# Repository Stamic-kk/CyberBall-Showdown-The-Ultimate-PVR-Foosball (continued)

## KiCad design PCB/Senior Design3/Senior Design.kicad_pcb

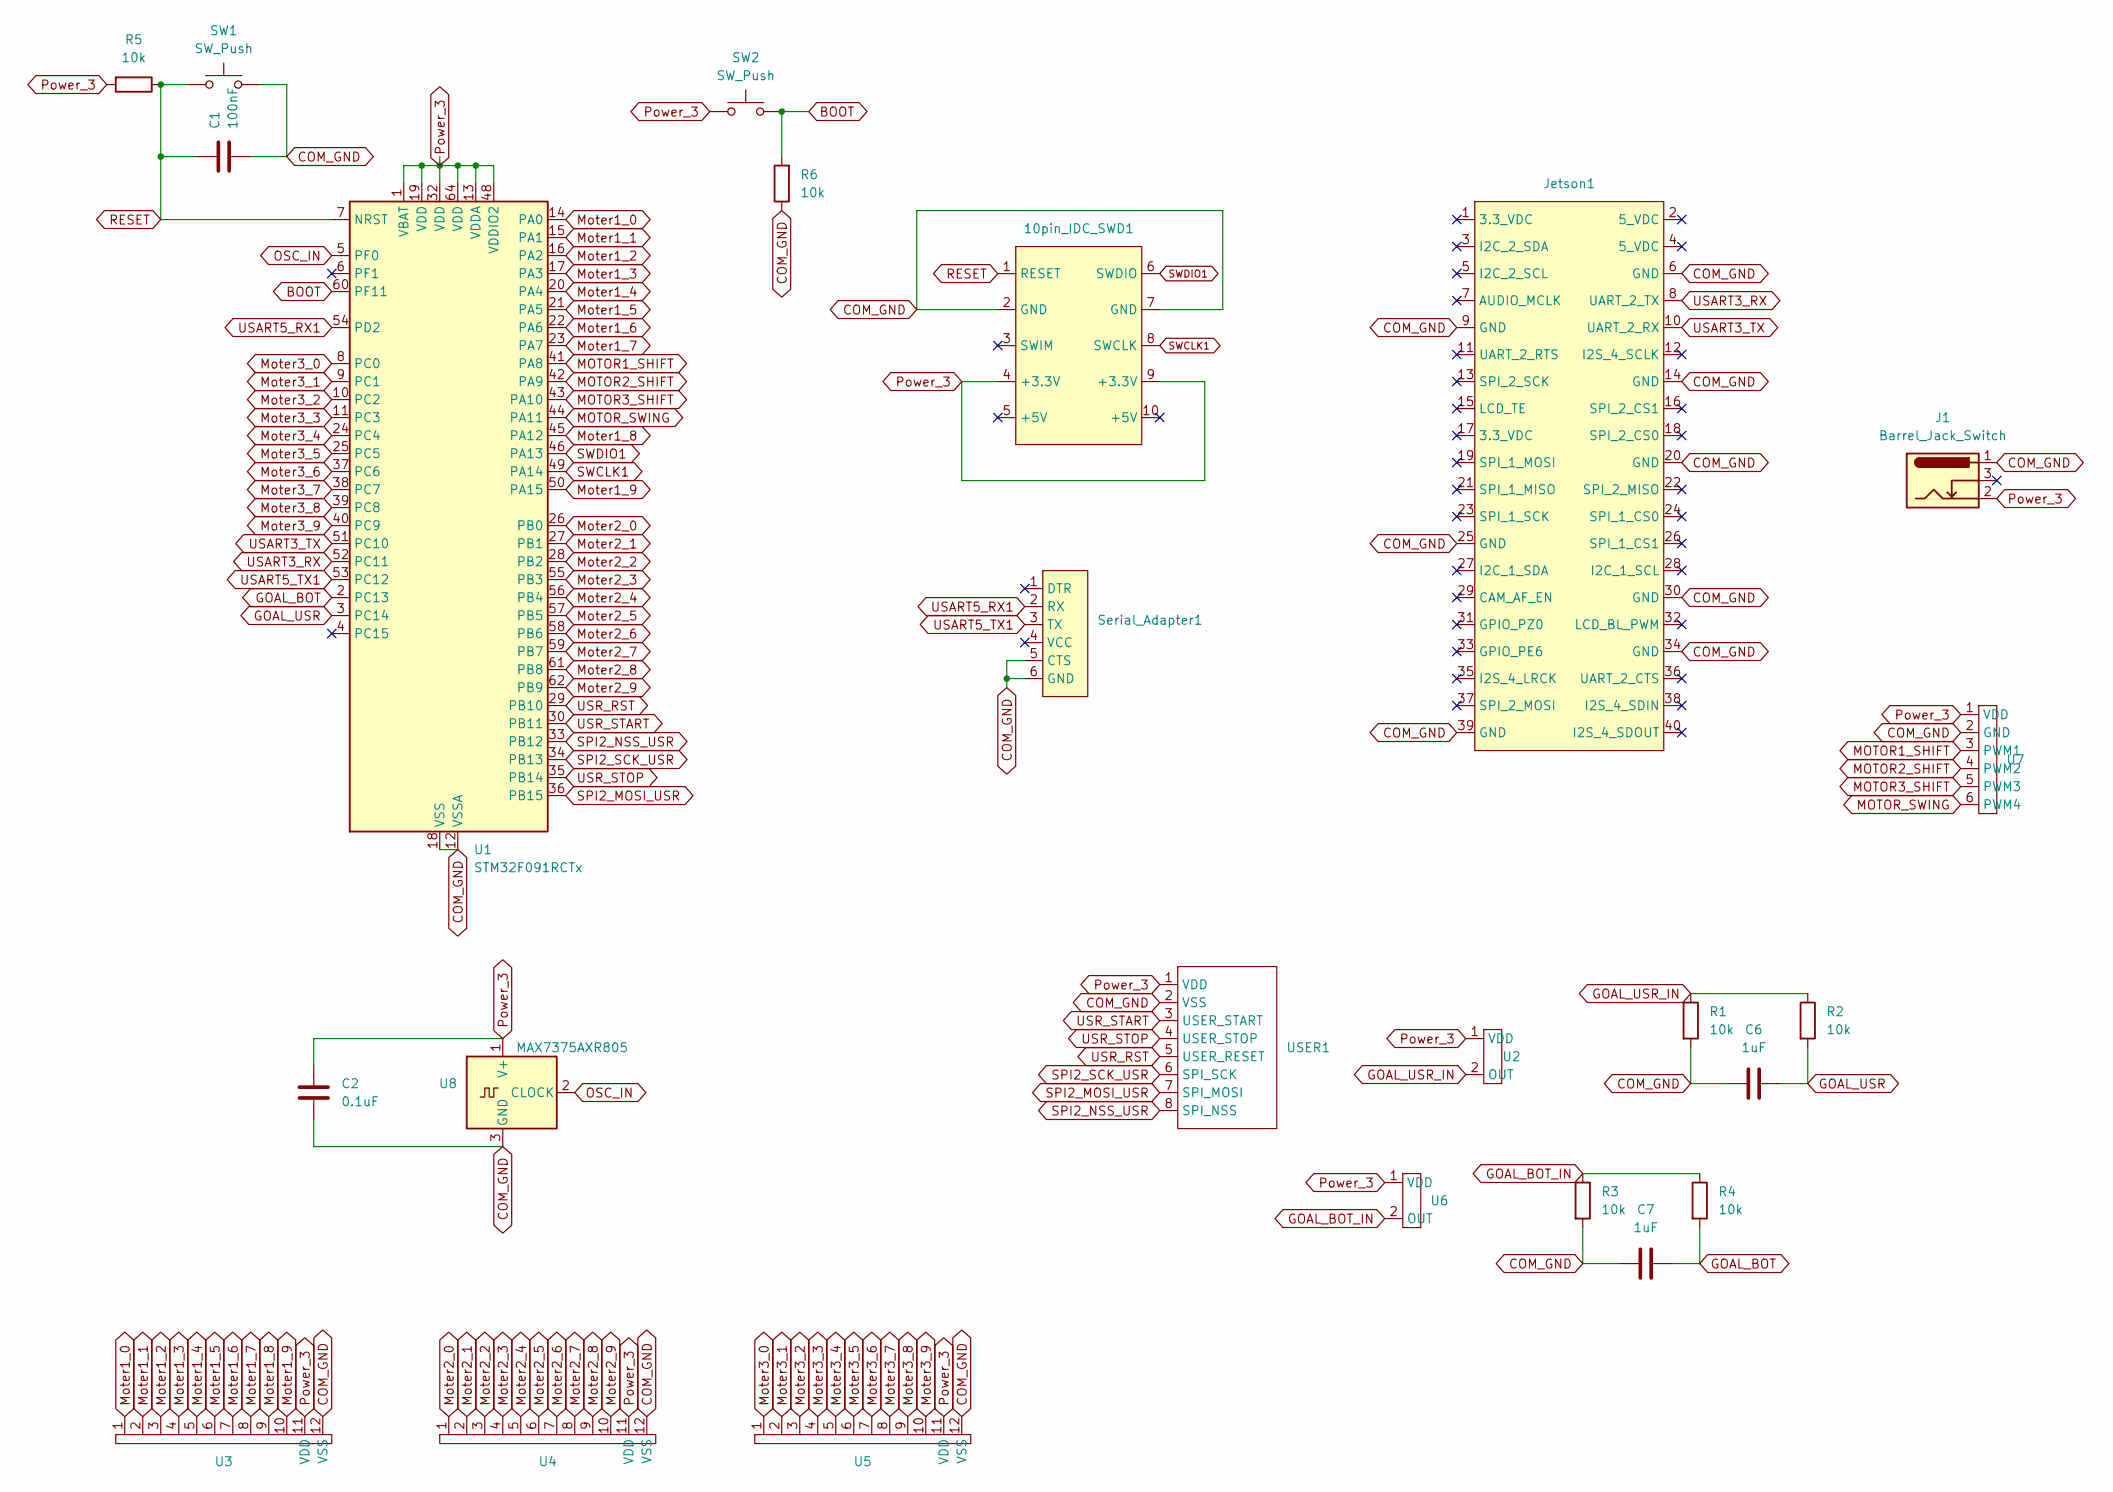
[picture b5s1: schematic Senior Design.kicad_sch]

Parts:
10pin_IDC_SWD1: 10idc
C1: 100nF; C_1206_3216Metric_Pad1.33x1.80mm_HandSolder
C2: 0.1uF; C_1206_3216Metric_Pad1.33x1.80mm_HandSolder
C6, C7: 1uF; C_1206_3216Metric_Pad1.33x1.80mm_HandSolder
J1: Barrel_Jack_Switch; BarrelJack_CUI_PJ-102AH_Horizontal
Jetson1: Jetson Nano
R1, R2, R3, R4, R5, R6: 10k; R_1206_3216Metric_Pad1.30x1.75mm_HandSolder
SW1, SW2: SW_Push; SW_PUSH_6mm_H4.3mm
Serial_Adapter1: Serial_port
U1: STM32F091RCTx; LQFP-64_10x10mm_P0.5mm
U2, U6: goal sensor
U3, U4, U5: Sensor Port
U7: Serial_port
U8: MAX7375AXR805; SOT-323_SC-70
USER1: User_Interface

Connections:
BOOT: R6.2, SW2.2, U1.60 (PF11)
COM_GND: 10pin_IDC_SWD1.2 (GND), 10pin_IDC_SWD1.7 (GND), C1.2, C2.2, C6.1, C7.1, J1.1, Jetson1.6 (GND), Jetson1.9 (GND), Jetson1.14 (GND), Jetson1.20 (GND), Jetson1.25 (GND), Jetson1.30 (GND), Jetson1.34 (GND), Jetson1.39 (GND), R1.2, R3.2, R6.1, SW1.2, Serial_Adapter1.5 (CTS), Serial_Adapter1.6 (GND), U1.12 (VSSA), U1.18 (VSS), U1.31 (VSS), U1.47 (VSS), U1.63 (VSS), U3.12 (VSS), U4.12 (VSS), U5.12 (VSS), U7.2 (GND), U8.3 (GND), USER1.2 (VSS)
GOAL_BOT: C7.2, R4.2, U1.2 (PC13)
GOAL_BOT_IN: R3.1, R4.1, U6.2 (OUT)
GOAL_USR: C6.2, R2.2, U1.3 (PC14)
GOAL_USR_IN: R1.1, R2.1, U2.2 (OUT)
MOTOR1_SHIFT: U1.41 (PA8), U7.3 (PWM1)
MOTOR2_SHIFT: U1.42 (PA9), U7.4 (PWM2)
MOTOR3_SHIFT: U1.43 (PA10), U7.5 (PWM3)
MOTOR_SWING: U1.44 (PA11), U7.6 (PWM4)
Moter1_0: U1.14 (PA0), U3.1
Moter1_1: U1.15 (PA1), U3.2
Moter1_2: U1.16 (PA2), U3.3
Moter1_3: U1.17 (PA3), U3.4
Moter1_4: U1.20 (PA4), U3.5
Moter1_5: U1.21 (PA5), U3.6
Moter1_6: U1.22 (PA6), U3.7
Moter1_7: U1.23 (PA7), U3.8
Moter1_8: U1.45 (PA12), U3.9
Moter1_9: U1.50 (PA15), U3.10
Moter2_0: U1.26 (PB0), U4.1
Moter2_1: U1.27 (PB1), U4.2
Moter2_2: U1.28 (PB2), U4.3
Moter2_3: U1.55 (PB3), U4.4
Moter2_4: U1.56 (PB4), U4.5
Moter2_5: U1.57 (PB5), U4.6
Moter2_6: U1.58 (PB6), U4.7
Moter2_7: U1.59 (PB7), U4.8
Moter2_8: U1.61 (PB8), U4.9
Moter2_9: U1.62 (PB9), U4.10
Moter3_0: U1.8 (PC0), U5.1
Moter3_1: U1.9 (PC1), U5.2
Moter3_2: U1.10 (PC2), U5.3
Moter3_3: U1.11 (PC3), U5.4
Moter3_4: U1.24 (PC4), U5.5
Moter3_5: U1.25 (PC5), U5.6
Moter3_6: U1.37 (PC6), U5.7
Moter3_7: U1.38 (PC7), U5.8
Moter3_8: U1.39 (PC8), U5.9
Moter3_9: U1.40 (PC9), U5.10
OSC_IN: U1.5 (PF0), U8.2 (CLOCK)
Power_3: 10pin_IDC_SWD1.4 (+3.3V), 10pin_IDC_SWD1.9 (+3.3V), C2.1, J1.2, R5.2, SW2.1, U1.1 (VBAT), U1.13 (VDDA), U1.19 (VDD), U1.32 (VDD), U1.48 (VDDIO2), U1.64 (VDD), U2.1 (VDD), U3.11 (VDD), U4.11 (VDD), U5.11 (VDD), U6.1 (VDD), U7.1 (VDD), U8.1 (V+), USER1.1 (VDD)
RESET: 10pin_IDC_SWD1.1 (RESET), C1.1, R5.1, SW1.1, U1.7 (NRST)
SPI2_MOSI_USR: U1.36 (PB15), USER1.7 (SPI_MOSI)
SPI2_NSS_USR: U1.33 (PB12), USER1.8 (SPI_NSS)
SPI2_SCK_USR: U1.34 (PB13), USER1.6 (SPI_SCK)
SWCLK1: 10pin_IDC_SWD1.8 (SWCLK), U1.49 (PA14)
SWDIO1: 10pin_IDC_SWD1.6 (SWDIO), U1.46 (PA13)
USART3_RX: Jetson1.8 (UART_2_TX), U1.52 (PC11)
USART3_TX: Jetson1.10 (UART_2_RX), U1.51 (PC10)
USART5_RX1: Serial_Adapter1.2 (RX), U1.54 (PD2)
USART5_TX1: Serial_Adapter1.3 (TX), U1.53 (PC12)
USR_RST: U1.29 (PB10), USER1.5 (USER_RESET)
USR_START: U1.30 (PB11), USER1.3 (USER_START)
USR_STOP: U1.35 (PB14), USER1.4 (USER_STOP)

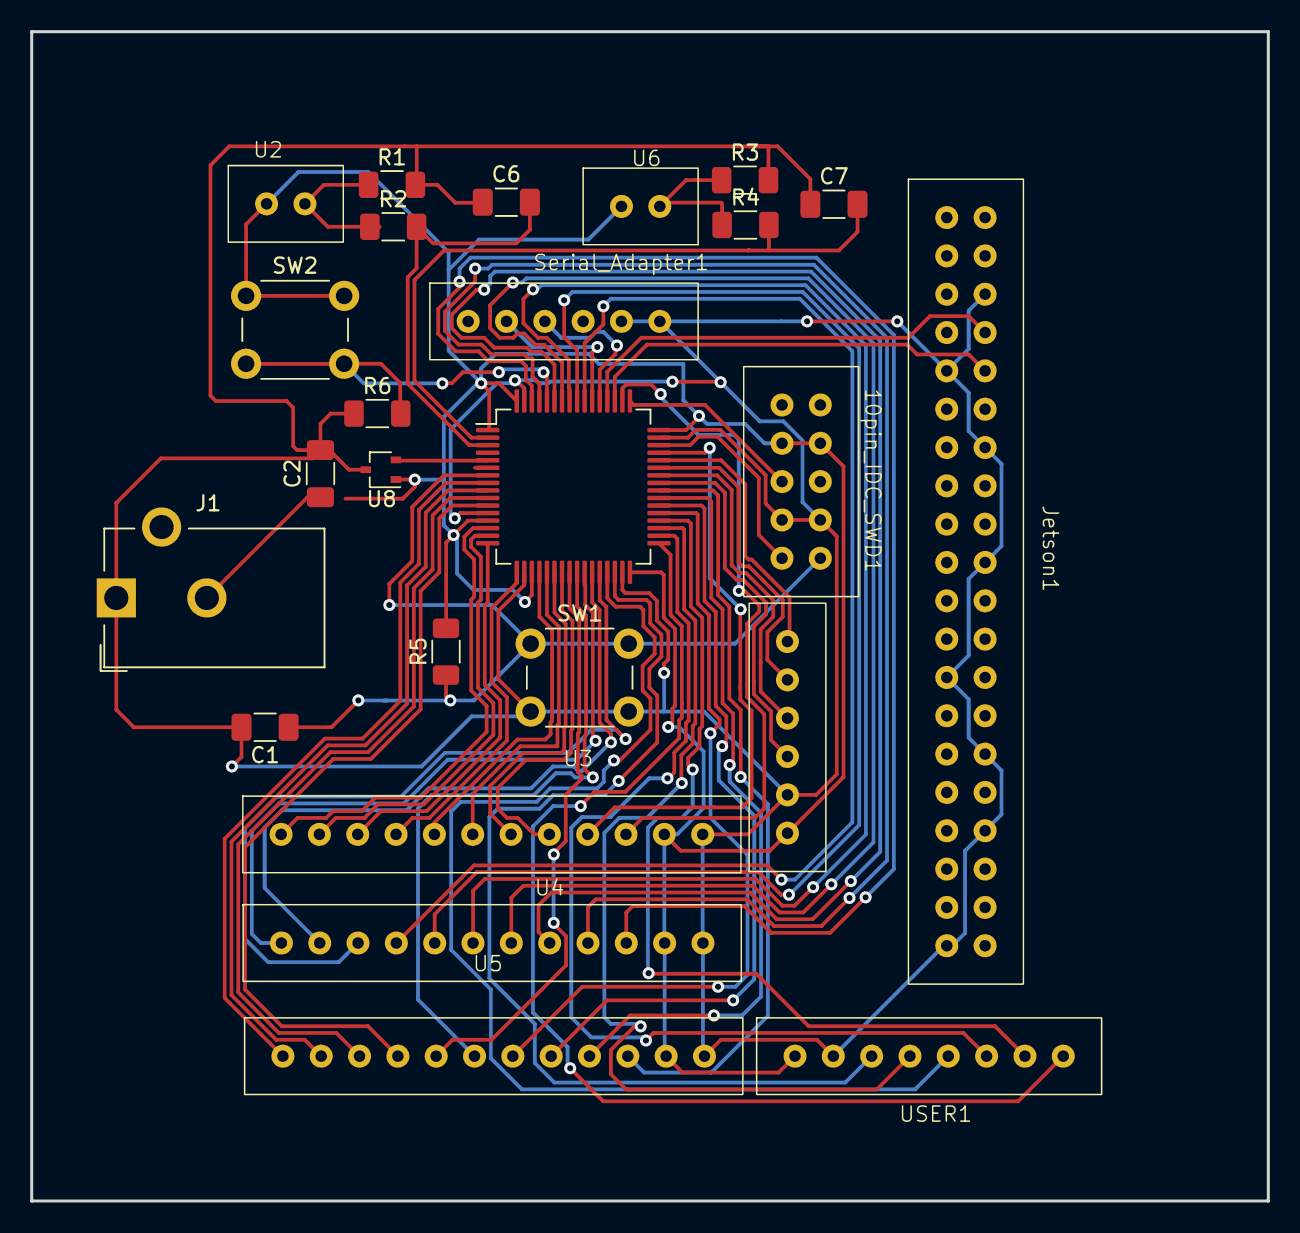
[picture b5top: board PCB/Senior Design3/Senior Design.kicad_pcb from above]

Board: 2 copper layers, 82.0 x 77.5 mm, 25 parts (0 on the bottom side), 55 nets.

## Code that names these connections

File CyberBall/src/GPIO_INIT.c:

#include <GPIO_INIT.h>

void init_GPIO_C(void){
	// PC 0-12
	RCC->AHBENR  |= RCC_AHBENR_GPIOCEN;
	GPIOC->MODER &= 0xf0000000; // clean PC 13-0

	//set PC 0-9 to input mode, PC 10 - 12 to Alternate function mode
	GPIOC->MODER |= 0x02A00000;

	//PC10 USART3_TX alt func 1
	//PC11 USART3_RX alt func 1
	//PC12 USART5_TX alt func 2
	GPIOC->AFR[1] &= ~(0x000fff00);
	GPIOC->AFR[1] |= 0x00021100;

	//PC 0-9 to PULL_UP
	GPIOC->PUPDR &= 0xf3f00000;
	GPIOC->PUPDR |= 0x04055555;
}

void init_GPIO_A(void){
	//PA 0 - 12 and PA15
	RCC->AHBENR   |= RCC_AHBENR_GPIOAEN;
	GPIOA->MODER  &= 0x3C000000; //clean PA 0-12, clean PA15

	//set PA 0-7 and 12, 15 to input mode, set PA 8-11   alter func mode
	GPIOA->MODER  |= 0x00aa0000;

	//PA8  TIM1_CH1 alt func 2
	//PA9  TIM1_CH2 alt func 2
	//PA10 TIM1_CH3 alt func 2
	//PA11 TIM1_CH4 alt func 2
	GPIOA->AFR[1] &= 0xffff0000;
	GPIOA->AFR[1] |= 0x00002222;

	//PA 0-7, 12, 15 to PULL_down
	GPIOA->PUPDR &= 0x3cff0000;
	GPIOA->PUPDR |= 0x41005555;

}

void init_GPIO_B(void){
	//PB 0 -15
	RCC->AHBENR  |= RCC_AHBENR_GPIOBEN;
	GPIOB->MODER &= 0x00000000;

	//set PB 0-11, 14 input mod4, 12,13,15 alt func
	GPIOB->MODER |= 0x8a000000;

	//PB12 SPI2_NSS alt func 0
	//PB13 SPI2_SCK alt func 0
	//PB15 SPI2_MOSI alt func 0
	GPIOB->AFR[1] &= 0x0f00ffff;

	//PB 0-9, 10,11, 14 to PULL_down
	GPIOB->PUPDR &= 0xcf000000;
	GPIOB->PUPDR |= 0x10555555;

}

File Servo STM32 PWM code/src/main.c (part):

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//     // TODO: Enable GPIO C
//     RCC->AHBENR |= RCC_AHBENR_GPIOCEN;

//     // TODO: Configure the PC6-9 to be the outputs of TIM3 Ch 1-4
//     // TODO: First we clear their MODER bits
//     GPIOC->MODER &= ~0xFF000;
//     // TODO: Then we set them to AF mode
//     GPIOC->MODER |= 0xAA000;
//     // TODO: Set PC6-9 to use AF0 since this corresponds to the TIM3 Ch1-4
//     // AFR[0] -> AFRL
//     // AFR[1] -> AFRH
//     GPIOC->AFR[0] &= ~0xFF000000;
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//    Enables the RCC clock to GPIOB and GPIOC without affecting any other RCC clock settings for other peripherals
    RCC->AHBENR |= RCC_AHBENR_GPIOBEN;
    RCC->AHBENR |= RCC_AHBENR_GPIOCEN;
//    Configures pins PB0 – PB10 to be outputs
    GPIOB->MODER &= ~0x3FFFFF;
    GPIOB->MODER |= 0x155555;
//    Configures pins PC4 – PC7 to be outputs
    GPIOC->MODER &= ~0xFF00;
    GPIOC->MODER |= 0x5500;
//    Configures pins PC4 – PC7 to have output type open-drain (using the OTYPER registers)
    GPIOC->OTYPER &= ~0xF0;
    GPIOC->OTYPER |= 0xF0;
//    Configures pins PC0 – PC3 to be inputs
//    Configures pins PC0 – PC3 to be internally pulled high
    GPIOC->PUPDR &= ~0xFF;
    GPIOC->PUPDR |= 0x55;

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// void setup_adc(void) {
// //    Enable the clock to GPIO Port A
//     RCC->AHBENR |= RCC_AHBENR_GPIOAEN;
// //    Set the configuration for analog operation only for the appropriate pin.    PA1 to analog 11
//     GPIOA->MODER &= ~0xC;
//     GPIOA->MODER |=  0xC;
// //    Enable the clock to the ADC peripheral
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
// //    Enable the clock to GPIO Port A (reenabling is safe)
//     RCC->AHBENR |= RCC_AHBENR_GPIOAEN;
// //    Set the configuration for analog operation only for the appropriate pin .  PA4, 11 for analog
//     GPIOA->MODER &= ~0x300;
//     GPIOA->MODER |=  0x300;
// //    Enable the RCC clock for the DAC
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
//    Activate the RCC clock to GPIO Port A.
    RCC->AHBENR |= RCC_AHBENR_GPIOAEN;
//    Configure the MODER for the four pins to set them for alternate function use.  (PA8,9,10,11 for  TIM1_CH1, TIM1_CH2, TIM1_CH3, and TIM1_CH4.
    GPIOA->MODER &= ~0xFF0000;
    // TODO: Then we set them to AF mode
    GPIOA->MODER |= 0xAA0000;
//    Set the alternate function register to route the timer function to the external pins.
    GPIOA->AFR[1] &= ~0xFFFF;    //PA8,9,10,11    clear first
    //to Set to route the timer function to the external pins. set to to AF2   0010
    GPIOA->AFR[1] |= 0x2222;

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{
    switch (channel)
    {
    case 1: TIM1->CCR1 = duty_cycle *240;       //TIM1 CH1: PA8
            break;
    case 2: TIM1->CCR2 = duty_cycle *240;       //TIM1 CH2: PA9
            break;
    case 3: TIM1->CCR3 = duty_cycle *240;       //TIM1 CH3: PA10
            break;
    case 4: TIM1->CCR4 = duty_cycle *240;       //TIM1 CH4: PA11
            break;
    }
}
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
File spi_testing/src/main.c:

///**
//  ******************************************************************************
//  * @file    main.c
//  * @author  Ac6
//  * @version V1.0
//  * @date    01-December-2013
//  * @brief   Default main function.
//  ******************************************************************************
//*/
//
//
//#include "stm32f0xx.h"
//#include "fifo.h"
//#include "tty.h"
//#include "usart.h"
//#include <stdio.h>
//#include <string.h> // for memmove()
//#include <stdlib.h>
//#include <stdint.h>
//
//void init_GPIO(){
//	//pa4 SPI1_NSS     |   pa15
//	//pa5 SPI1_SCK	   |   pa5
//	//pa7 SPI1_MOSI    |   pa6
//    RCC->APB2ENR|= RCC_APB2ENR_SPI1EN;
//    RCC->AHBENR |= RCC_AHBENR_GPIOAEN;
//    GPIOA->MODER &=~(0x3f<<10);
//    GPIOA->MODER |= (0x2A<<10);
//    GPIOA->MODER &=~(0x3<<30);
//    GPIOA->MODER |=(0x2<<30);
//    GPIOA->AFR[0]&=~(0xfff<<(5*4));
//    GPIOA->AFR[1]&=~(0xf<<((15-8)*4));
//}
//
//void init_spi(){
//	RCC->APB2ENR|= RCC_APB2ENR_SPI1EN;
//	SPI1->CR1 &= ~(SPI_CR1_SPE);
//
//	SPI1->CR1 &= ~(SPI_CR1_MSTR); //set the device to slave mode
//	SPI1->CR1 |= SPI_CR1_BR;
//	SPI1->CR2 |= SPI_CR2_DS_0|SPI_CR2_DS_3;
//	SPI1->CR2 &= ~(SPI_CR2_DS_1|SPI_CR2_DS_2);
//
//	SPI1->CR1 |= SPI_CR1_SPE;
//}
//
//int data_rec(){
//	int data;
//	while(SPI1->SR & SPI_SR_BSY){}
//	data = SPI1->DR;
//	return data;
//}
//
//
//int main(void)
//{
//	init_usart5();
//
//	int data = 0;
////	init_GPIO();
////	init_spi();
//    setbuf(stdin,0);
//    setbuf(stdout,0);
//    setbuf(stderr,0);
////	while(1){
////		printf("data: \n");
//////		data = data_rec();
//////		printf("data: %d\n", data);
////	}
//    for(int i = 0; i < 10; i++){
//    	printf("Incremental Printout Test %d\n", i);
//    }
//}
//
//

/**
  ******************************************************************************
  * @file    main.c
  * @author  Ac6
  * @version V1.0
  * @date    01-December-2013
  * @brief   Default main function.
  ******************************************************************************
*/

#include "stm32f0xx.h"
#include "usart.h"


#include "fifo.h"
#include "tty.h"
#include <stdio.h>
#include <string.h> // for memmove()
#include <stdlib.h>
// PD2 use for USART RX
// PC12 use for USART TX




int main(void)
{
    init_usart5();
//    setup_adc();
//    init_tim2();
//    //spi_display();

    setbuf(stdin,0);
    setbuf(stdout,0);
    setbuf(stderr,0);

    for(int i = 0; i < 10; i++){
    	printf("Incremental Printout Test %d\n", i);
    }
	for(;;);
}

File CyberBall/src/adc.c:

#include "adc.h"
//#include "stm32f0xx.h"
void setup_adc(void) {
    RCC -> AHBENR |= RCC_AHBENR_GPIOAEN;

    GPIOA -> MODER &= ~0x0000000c;
    GPIOA -> MODER |= 0x0000000c;                  //PA1 is used to be the input of ADC1

    GPIOA -> MODER &= ~0x00000030;
    GPIOA -> MODER |= 0x00000030;                  //PA2 is used as second input of ADC1

    GPIOA -> MODER &= ~0x000003c0;                 //config PA3 and PA4
    GPIOA -> MODER |= 0x000003c0;



    RCC -> APB2ENR |= RCC_APB2ENR_ADC1EN;
    RCC -> CR2 |= RCC_CR2_HSI14ON;
    while ((RCC -> CR2 & RCC_CR2_HSI14RDY) == 0){
        ;
    }
    ADC1 -> CR |= ADC_CR_ADEN;                     //Enable ADC before further config
    while ((ADC1 -> ISR & ADC_ISR_ADRDY) == 0){
        ;
    }

    //enable channel 1 and channel 2 for ADC
    ADC1 -> CHSELR |= ADC_CHSELR_CHSEL1;            //Since PA1 is used, we should select channel 1
    while ((ADC1 -> ISR & ADC_ISR_ADRDY) == 0){
            ;
    }
    ADC1 -> CHSELR |= ADC_CHSELR_CHSEL2;            //Since PA2 is used, we should select channel 2
	while ((ADC1 -> ISR & ADC_ISR_ADRDY) == 0){
			;
	}

    ADC1 -> CHSELR |= ADC_CHSELR_CHSEL3;            //Since PA1 is used, we should select channel 3
    while ((ADC1 -> ISR & ADC_ISR_ADRDY) == 0){
            ;
    }
    ADC1 -> CHSELR |= ADC_CHSELR_CHSEL4;            //Since PA2 is used, we should select channel 4
	while ((ADC1 -> ISR & ADC_ISR_ADRDY) == 0){
			;
	}

	//set scan sequence direction
	ADC1 -> CFGR1 = ADC_CFGR1_SCANDIR;
	while ((ADC1 -> ISR & ADC_ISR_ADRDY) == 0){
			;
	}

//	ADC1 -> CFGR1 |= 0x00001000;
//	while ((ADC1 -> ISR & ADC_ISR_ADRDY) == 0){
//			;
//	}
}

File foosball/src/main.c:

/**
  ******************************************************************************
  * @file    main.c
  * @author  Ac6
  * @version V1.0
  * @date    01-December-2013
  * @brief   Default main function.
  ******************************************************************************
*/


#include "stm32f0xx.h"
#include <stdint.h>

void initb();
void initc();
void setn(int32_t pin_num, int32_t val);
int32_t readpin(int32_t pin_num);
void buttons(void);
void keypad(void);

void mysleep(void) {
    for(int n = 0; n < 1000; n++);
}

int main(void) {
    // Uncomment when most things are working
  //  autotest();

//    initb();
//    initc();

    // uncomment one of the loops, below, when ready
    // while(1) {
    //   buttons();
    // }

    // while(1) {
    //   keypad();
    // }
    RCC->AHBENR |= RCC_AHBENR_GPIOCEN;
    GPIOC->MODER &= ~GPIO_MODER_MODER6;
    GPIOC->MODER |= GPIO_MODER_MODER6_0;
    GPIOC -> ODR |= 0x40;

    for(;;);
}

/**
 * @brief Init GPIO port B
 *        Pin 0: input
 *        Pin 4: input
 *        Pin 8-11: output
 *
 */
void initb() {
    int32_t mask = 0x3;
    RCC->AHBENR |= RCC_AHBENR_GPIOBEN;
    GPIOB->MODER &= ~mask;
    mask = mask <<8;
    GPIOB->MODER &= ~mask;
    mask = 0x55 <<16;
    GPIOB->MODER &= ~(0xFF<<16);
    GPIOB->MODER |= mask;
}

/**
 * @brief Init GPIO port C
 *        Pin 0-3: inputs with internal pull down resistors
 *        Pin 4-7: outputs
 *
 */
void initc() {
    RCC->AHBENR |= RCC_AHBENR_GPIOCEN;
    int32_t mask = 0xFF;
    GPIOC->MODER &= ~mask;
    GPIOC->PUPDR &= ~0xFF;
    GPIOC->PUPDR |= 0xAA;
    mask = 0x55 <<8;
    GPIOC->MODER &= ~(0xFF<<8);
    GPIOC->MODER |= mask;
}

/**
 * @brief Set GPIO port B pin to some value
 *
 * @param pin_num: Pin number in GPIO B
 * @param val    : Pin value, if 0 then the
 *                 pin is set low, else set high
 */
void setn(int32_t pin_num, int32_t val) {
    if(val !=0)
    {
        val = 1<<pin_num;
        GPIOB->ODR |= val;
    }
    else
    {
        val = 1<<pin_num;
        GPIOB->BRR |= val;
    }
}

/**
 * @brief Read GPIO port B pin values
 *
 * @param pin_num   : Pin number in GPIO B to be read
 * @return int32_t  : 1: the pin is high; 0: the pin is low
 */
int32_t readpin(int32_t pin_num) {
    int32_t ret = GPIOB->IDR;
    ret = (ret>>pin_num) & 0x1;
    return ret;
}

/**
 * @brief Control LEDs with buttons
 *        Use PB0 value for PB8
 *        Use PB4 value for PB9
 *
 */
void buttons(void) {
    int32_t PB0 = readpin(0);
    setn(8,PB0);
    int32_t PB4 = readpin(4);
    setn(9,PB4);
}

/**
 * @brief Control LEDs with keypad
 *
 */
void keypad(void) {
    for(int i =1; i<5;i++)
    {
        GPIOC->ODR &=0;
        GPIOC->ODR |= (0x1<<(3+i));
        mysleep();
        int32_t in = (GPIOC->IDR & 0xF);
        setn(7+i, in);
    }
}

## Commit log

2024-01-15 initial
2024-01-17 move to cube IDE
2024-01-17 add link
2024-01-17 move old files
2024-01-19 revision
2024-01-19 add usart serial port
2024-01-21 CV test
2024-01-22 add cpp vpi example
2024-01-23 vpi1.2
2024-01-23 worked adc mag
2024-01-23 add jetson comp version
2024-01-23 add cv output
2024-01-24 add predictor
2024-01-24 add main routine
2024-01-29 add Kalman filter supports
2024-01-29 re-config
2024-01-29 add sth
2024-01-29 conflict
2024-01-31 Kalman backup
2024-01-31 ADC SPI
2024-01-31 sync
2024-02-06 fix cmake
2024-02-06 update experiment
2024-02-07 working spi
2024-02-09 back up
2024-02-14 working live tracking
2024-02-15 clean
2024-02-20 PCB Add
2024-02-21 save
2024-02-21 PCB Library added
2024-02-21 main board completed
2024-02-21 conf usart
2024-02-22 fix usart
2024-02-22 pcb modified
2024-02-23 GPIOs
2024-02-23 main board mod
2024-02-23 better frame rate
2024-02-24 clock mod
2024-02-26 more space on mainboard
2024-02-26 change footprint hall
2024-02-26 change footprint hall2
2024-02-27 silkcreen added
2024-02-27 footprint mod
2024-02-28 mod xxx
2024-02-28 decoupling completed
2024-02-28 decoupling completed2
2024-02-29 CAD added
2024-02-29 power board added
2024-02-29 schematic organized
2024-02-29 pdf schematic added
2024-03-02 update fps
2024-03-02 rm unnecessary
2024-03-04 Power footprint
2024-03-04 lm2596 mod
2024-03-04 small mod
2024-03-05 upload servo PWM control v1
2024-03-05 update gitignore
2024-03-05 make frame rate variable
2024-03-06 connector changed
2024-03-06 GND hole added
2024-03-06 lib mod
2024-03-06 barrel mod
2024-03-06 barrel mod2
2024-03-06 save for resolving conflict
2024-03-06 remove rebundant file
2024-03-07 via hole not tented
2024-03-08 gerber zipped
2024-03-18 backup
2024-03-25 working interrupt servo
2024-03-27 better prediction
2024-03-27 working prediction, no control
2024-03-28 basic defense
2024-04-03 uart sending pos for all three lines
2024-04-04 Finish servo move
2024-04-05 rewrite hall
2024-04-08 closest player
2024-04-12 correct coordinates
2024-04-16 basically work
2024-04-18 for demo
2024-04-18 update read me
2024-04-18 update files
2024-04-18 For fun
2024-04-18 change project name
2024-04-19 after demo
2024-04-19 fix a bug that blocks filter initialization
2024-04-19 update location record
2024-04-22 smarter
2024-04-24 stable version
2024-04-25 only the mid doesnot work
2024-04-25 update mcu
